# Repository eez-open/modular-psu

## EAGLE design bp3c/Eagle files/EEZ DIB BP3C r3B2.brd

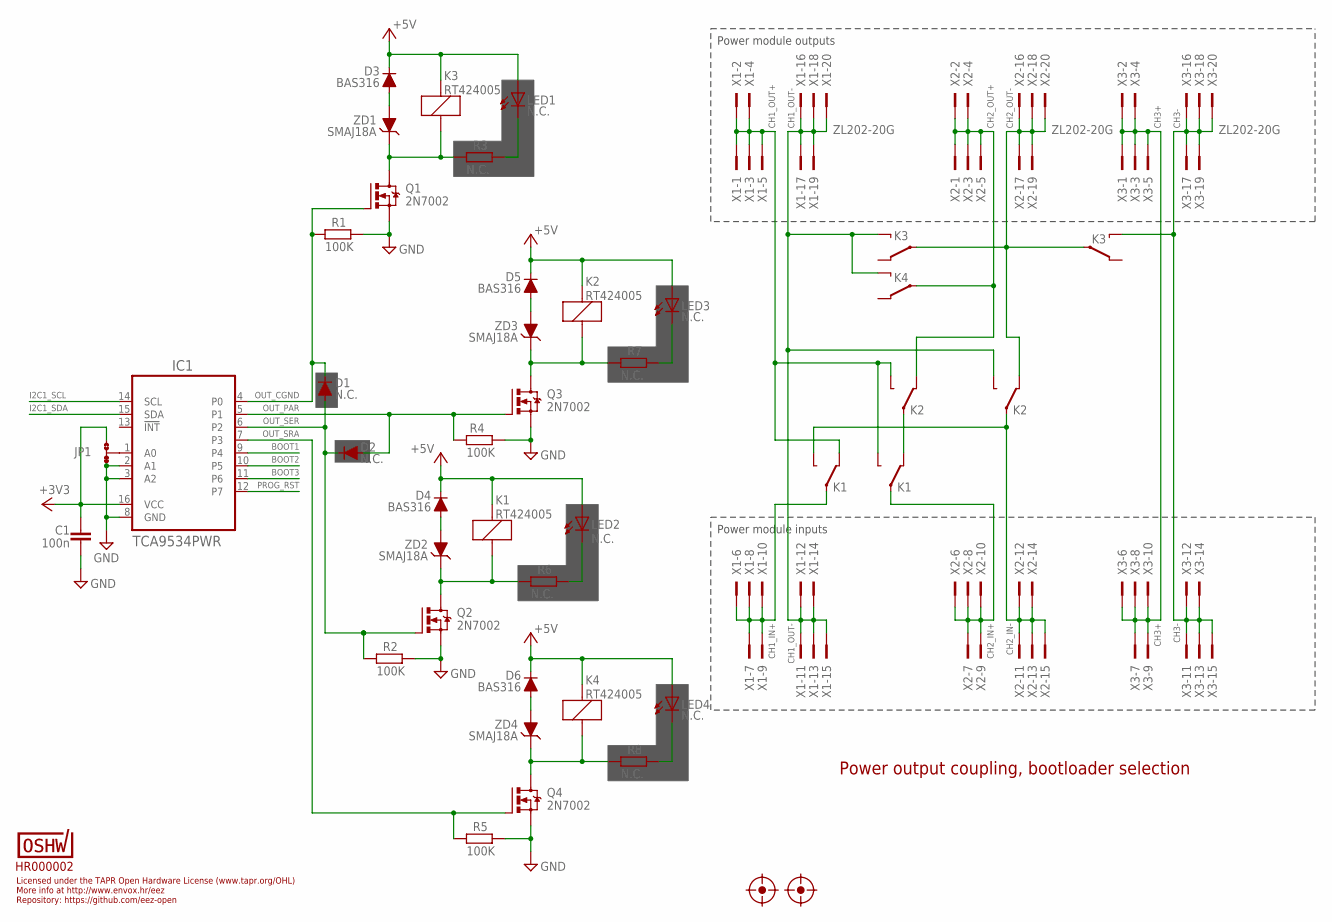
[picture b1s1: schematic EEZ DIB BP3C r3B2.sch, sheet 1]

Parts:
C1: 100n; C0603
D1, D2: N.C.; SOD323-R
D3, D4, D5, D6: BAS316; SOD323-R
FM1, FM2: FIDUCIAL
IC1: TCA9534PWR; PW(R-PDSO-G16)
JP1: JP3-CUT
K1, K2, K3, K4: RT424005; RT-C/016A5_ROUND
LED1, LED2, LED3, LED4: N.C.; LED_0805
OSHWA: HR000002; CERT-SMALL-SILK
Q1, Q2, Q3, Q4: 2N7002; SOT103P240X110-3N; MPN 2N7002-7-F
R1, R2, R4, R5: 100K; R0805
R3, R6, R7, R8: N.C.; R0805
X1, X2, X3: ZL202-20G; DS1021-2*10SF11
ZD1, ZD2, ZD3, ZD4: SMAJ18A; DO214AC

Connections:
+3V3: C1.1, IC1.16 (VCC), JP1.NO; also elsewhere on the board
+5V: D3.C, D4.C, D5.C, D6.C, K1.A2 (C1), K2.A2 (C1), K3.A2 (C1), K4.A2 (C1), LED1.A, LED2.A, LED3.A, LED4.A; also elsewhere on the board
BOOT1: IC1.9 (P4); also elsewhere on the board
BOOT2: IC1.10 (P5); also elsewhere on the board
BOOT3: IC1.11 (P6); also elsewhere on the board
CH1_IN+: K1.11A, X1.6, X1.7, X1.8, X1.9, X1.10
CH1_OUT+: K1.12A (S), K1.14B (O), K2.14A (O), X1.1, X1.2, X1.3, X1.4, X1.5
CH1_OUT-: K2.14B (O), K3.14A (O), K4.14A (O), X1.11, X1.12, X1.13, X1.14, X1.15, X1.16, X1.17, X1.18, X1.19, X1.20
CH2_IN+: K1.11B, X2.6, X2.7, X2.8, X2.9, X2.10
CH2_IN-: K1.14A (O), K2.11B, X2.11, X2.12, X2.13, X2.14, X2.15
CH2_OUT+: K2.12A (S), K4.11A, X2.1, X2.2, X2.3, X2.4, X2.5
CH2_OUT-: K2.12B (S), K3.11A, K3.11B, X2.16, X2.17, X2.18, X2.19, X2.20
CH3+: X3.1, X3.2, X3.3, X3.4, X3.5, X3.6, X3.7, X3.8, X3.9, X3.10
CH3-: K3.14B (O), X3.11, X3.12, X3.13, X3.14, X3.15, X3.16, X3.17, X3.18, X3.19, X3.20
GND: C1.2, IC1.2 (A1), IC1.3 (A2), IC1.8 (GND), JP1.NC, Q1.2 (S), Q2.2 (S), Q3.2 (S), Q4.2 (S), R1.1, R2.1, R4.1, R5.1; also elsewhere on the board
I2C1_SCL: IC1.14 (SCL); also elsewhere on the board
I2C1_SDA: IC1.15 (SDA); also elsewhere on the board
unnamed: LED2.C, R6.1
unnamed: LED3.C, R7.1
unnamed: IC1.1 (A0), JP1.COM
unnamed: K3.A1 (C2), Q1.3 (D), R3.2, ZD1.C
unnamed: D3.A, ZD1.A
unnamed: LED1.C, R3.1
unnamed: K4.A1 (C2), Q4.3 (D), R8.2, ZD4.C
unnamed: D6.A, ZD4.A
unnamed: LED4.C, R8.1
unnamed: K1.A1 (C2), Q2.3 (D), R6.2, ZD2.C
unnamed: K2.A1 (C2), Q3.3 (D), R7.2, ZD3.C
unnamed: D4.A, ZD2.A
unnamed: D5.A, ZD3.A
OUT_CGND: D1.C, IC1.4 (P0), Q1.1 (G), R1.2
OUT_PAR: D2.A, IC1.5 (P1), Q3.1 (G), R4.2
OUT_SER: D1.A, D2.C, IC1.6 (P2), Q2.1 (G), R2.2
OUT_SRA: IC1.7 (P3), Q4.1 (G), R5.2
PROG_RST: IC1.12 (P7); also elsewhere on the board
SER_PAR: K1.12B (S), K2.11A

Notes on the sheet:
Licensed under the TAPR Open Hardware License (www.tapr.org/OHL)
Repository: https://github.com/eez-open
More info at http://www.envox.hr/eez
Power output coupling, bootloader selection
Power module inputs
Power module outputs

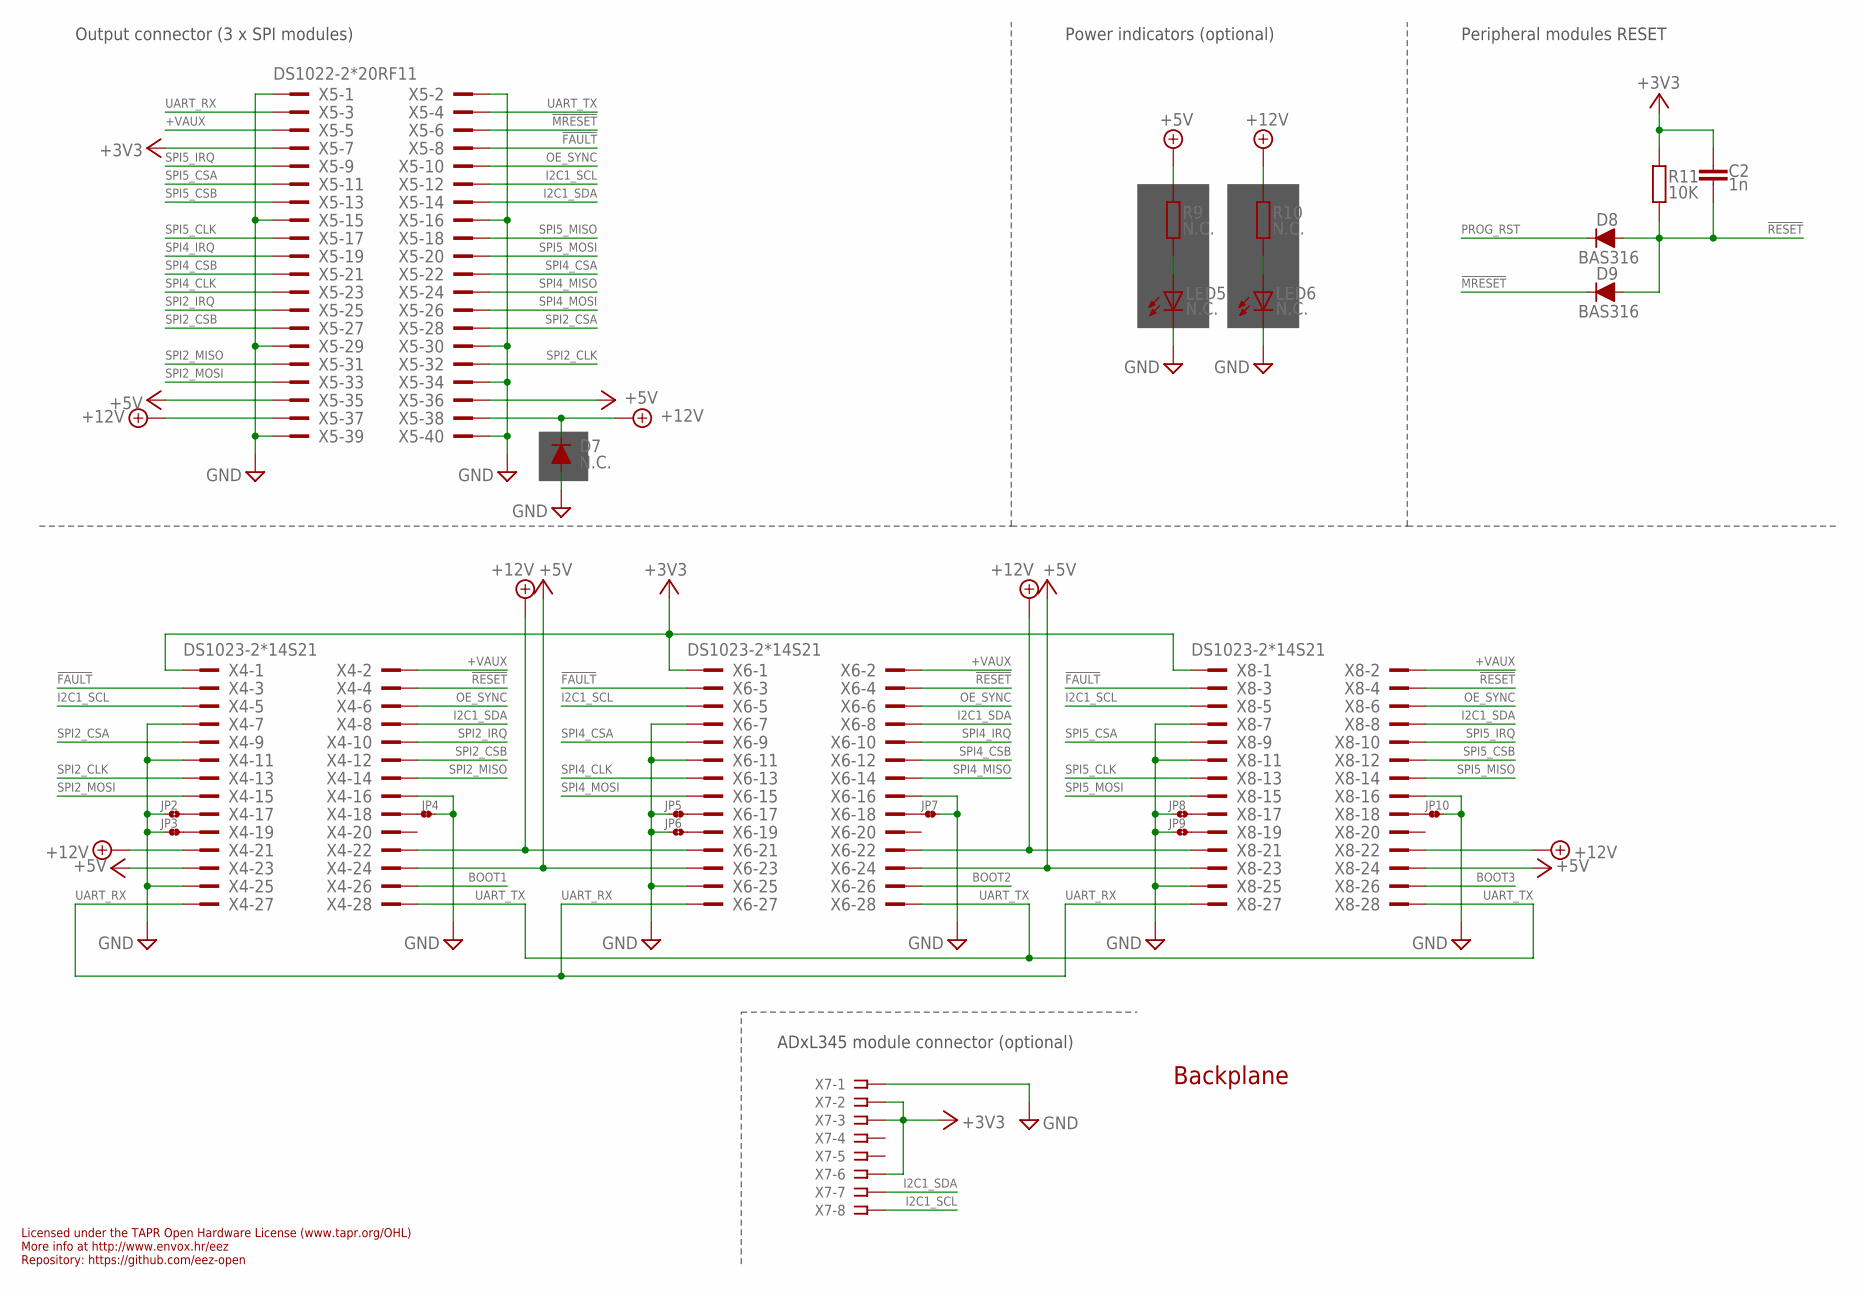
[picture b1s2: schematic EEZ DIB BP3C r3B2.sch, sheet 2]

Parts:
C2: 1n; C0805
D7: N.C.; DO214AA
D8, D9: BAS316; SOD323-R
JP2, JP6, JP8, JP9: JP2-CUT
JP3, JP4, JP5, JP7, JP10: JP2-NOCUT
LED5, LED6: N.C.; LED_0805
R9, R10: N.C.; R0805
R11: 10K; R0805
X4, X6, X8: DS1023-2*14S21; TSW-114-07-F-D
X5: DS1022-2*20RF11; ZL212-40KG
X7: N.C.; SSW-108-02-S-S

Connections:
!FAULT: X4.3, X5.8, X6.3, X8.3
!MRESET: D9.C, X5.6
!RESET: C2.1, D8.A, D9.A, R11.2, X4.4, X6.4, X8.4
+3V3: C2.2, R11.1, X4.1, X5.7, X6.1, X7.2, X7.3, X7.6, X8.1; also elsewhere on the board
+5V: R9.1, X4.23, X4.24, X5.35, X5.36, X6.23, X6.24, X8.23, X8.24; also elsewhere on the board
+12V: D7.C, R10.1, X4.21, X4.22, X5.37, X5.38, X6.21, X6.22, X8.21, X8.22
+VAUX: X4.2, X5.5, X6.2, X8.2
BOOT1: X4.26; also elsewhere on the board
BOOT2: X6.26; also elsewhere on the board
BOOT3: X8.26; also elsewhere on the board
GND: D7.A, JP2.1, JP3.1, JP4.2, JP5.1, JP6.1, JP7.2, JP8.1, JP9.1, JP10.2, LED5.C, LED6.C, X4.7, X4.11, X4.16, X4.25, X5.1, X5.2, X5.15, X5.16, X5.29, X5.30, X5.34, X5.39, X5.40, X6.7, X6.11, X6.16, X6.25, X7.1, X8.7, X8.11, X8.16, X8.25; also elsewhere on the board
I2C1_SCL: X4.5, X5.12, X6.5, X7.8, X8.5; also elsewhere on the board
I2C1_SDA: X4.8, X5.14, X6.8, X7.7, X8.8; also elsewhere on the board
unnamed: JP4.1, X4.18
unnamed: LED5.A, R9.2
unnamed: LED6.A, R10.2
unnamed: JP2.2, X4.17
unnamed: JP3.2, X4.19
unnamed: JP7.1, X6.18
unnamed: JP5.2, X6.17
unnamed: JP6.2, X6.19
unnamed: JP10.1, X8.18
unnamed: JP8.2, X8.17
unnamed: JP9.2, X8.19
OE_SYNC: X4.6, X5.10, X6.6, X8.6
PROG_RST: D8.C; also elsewhere on the board
SPI2_CLK: X4.13, X5.32
SPI2_CSA: X4.9, X5.28
SPI2_CSB: X4.12, X5.27
SPI2_IRQ: X4.10, X5.25
SPI2_MISO: X4.14, X5.31
SPI2_MOSI: X4.15, X5.33
SPI4_CLK: X5.23, X6.13
SPI4_CSA: X5.22, X6.9
SPI4_CSB: X5.21, X6.12
SPI4_IRQ: X5.19, X6.10
SPI4_MISO: X5.24, X6.14
SPI4_MOSI: X5.26, X6.15
SPI5_CLK: X5.17, X8.13
SPI5_CSA: X5.11, X8.9
SPI5_CSB: X5.13, X8.12
SPI5_IRQ: X5.9, X8.10
SPI5_MISO: X5.18, X8.14
SPI5_MOSI: X5.20, X8.15
UART_RX: X4.27, X5.3, X6.27, X8.27
UART_TX: X4.28, X5.4, X6.28, X8.28

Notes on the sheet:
Licensed under the TAPR Open Hardware License (www.tapr.org/OHL)
Repository: https://github.com/eez-open
More info at http://www.envox.hr/eez
Backplane
Output connector (3 x SPI modules)
Power indicators (optional)
Peripheral modules RESET
ADxL345 module connector (optional)

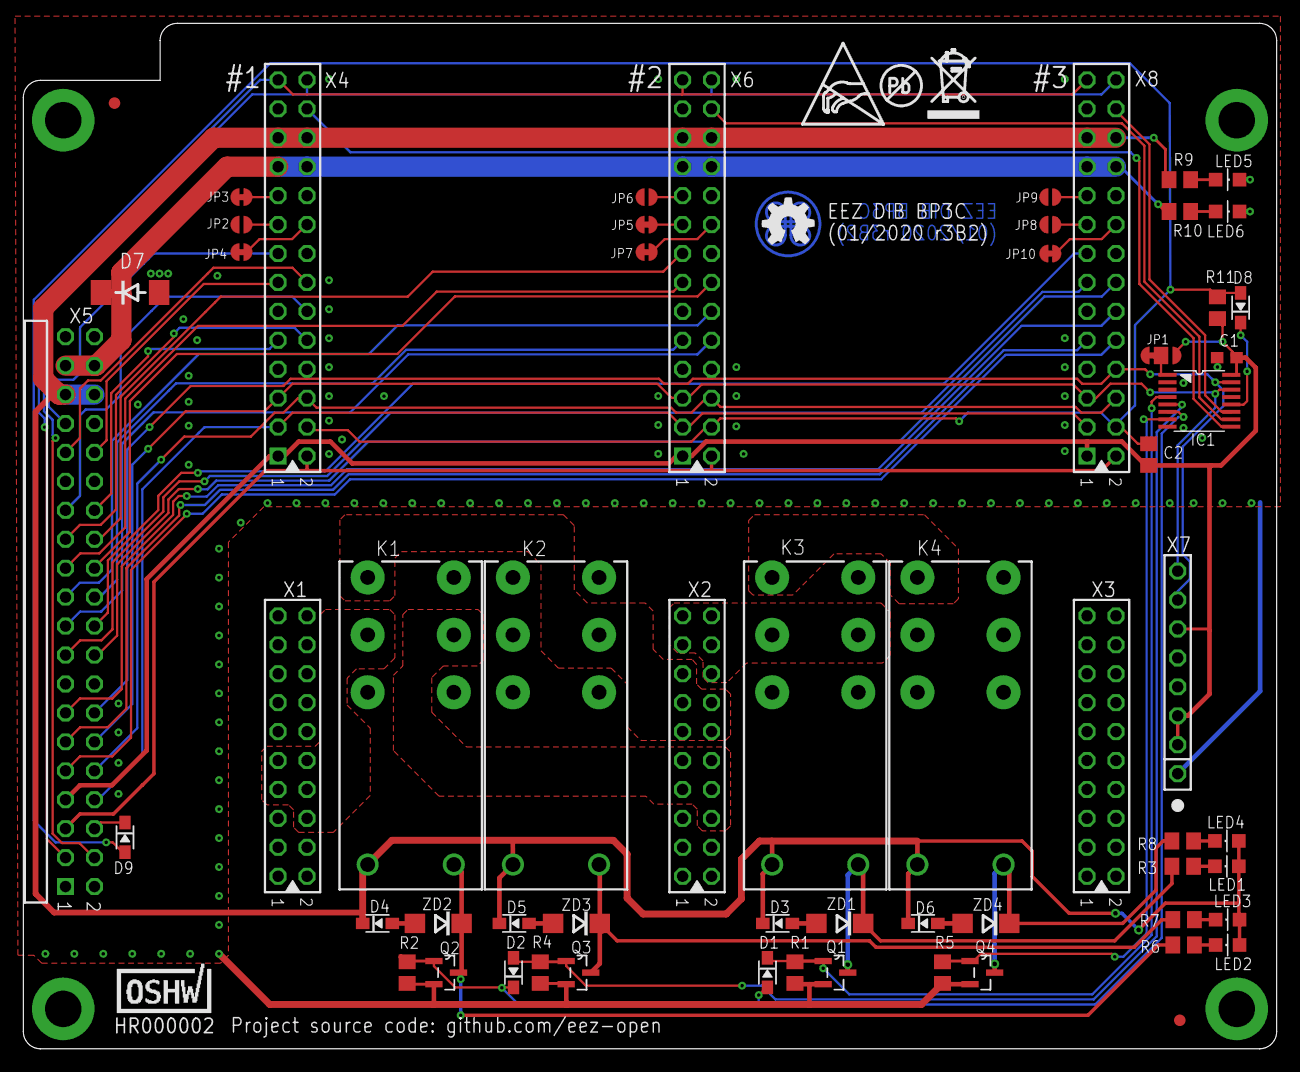
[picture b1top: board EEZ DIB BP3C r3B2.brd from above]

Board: 2 copper layers, 110.0 x 90.0 mm, 66 parts (0 on the bottom side), 73 nets.

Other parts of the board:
EEZ_SIGNATURE: SIGNATURESMALL; SIGNATURE_5MM
U$2: RECYCLE_BIN1/8
U$4: ESD_SYMBOL
U$5: PB_SMALL

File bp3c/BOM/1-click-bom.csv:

References,Qty,Description,Manufacturer,MPN,Manufacturer,MPN,Manufacturer,MPN,Manufacturer,MPN,Manufacturer,MPN,Manufacturer,MPN,Digikey,Mouser,RS,Newark,Farnell
C1,1,100n,,C0603C104K4RAC7081,KEMET,C0603C104K4RAC7081,KEMET,C0603C104K4RACTU,KEMET,C0603C104M4RACTU,Murata,GCM188R71C104KA37D,,,490-4774-6-ND,80C0603C104M4R,2644630,,2522597
C2,1,1n,,VJ0805A102JXACW1BC,Würth Elektronik,885012007040,Würth Elektronik,885012007063,Vishay,VJ0805A102JXACW1BC,,,,,720-1634-6-ND,710885012007063,1927618,,2533866
"D3, D4, D5, D6, D8, D9",6,BAS316,,"BAS316,115",Nexperia,BAS316,Nexperia,"BAS316,115",Nexperia,BAS316Z,,,,,1727-4309-6-ND,771BAS316T/R,3972914,,8734275
IC1,1,TCA9534PWR,Texas Instruments,TCA9534PWR,Texas Instruments,TCA9535PWR,,,,,,,,,296-25129-6-ND,595TCA9535PWR,8143997,,3124760
"K1, K2, K3, K4",4,RT424005,,RT424005,TE Connectivity,5-1393243-9,,,,,,,,,PB1998-ND,655RT424005,,,1629052
"Q1, Q2, Q3, Q4",4,2N7002,,2N7002K-7,ON Semiconductor,2N7002,Diodes Inc.,2N7002K-7,Toshiba,"T2N7002AK,LM",,,,,2N7002K-7DIDKR-ND,5122N7002,6710312,,9845313
"R1, R2, R4, R5",4,100K,,MCWR08X1003FTL,Vishay,CRCW0805100KFKEAC,TE Connectivity,CRG0805F100K,Multicomp,MCWR08X1003FTL,Stackpole Electronics,RMCF0805FT100K,,,RMCF0805FT100KDKR-ND,71CRCW0805100KFKEAC,2230691,,2447551
R11,1,10K,,RC0805FR-0710KL,TE Connectivity,CRG0805F10K,Yageo,RC0805FR-0710KL,,,,,,,311-10.0KCRCT-ND,603RC0805FR0710KL,1251189,,2148862
"X1, X2, X3",3,DS1021-2*10SF11,FCI,77313-802-20LF,,,,,,,,,,,77313-802-20LF-ND,6497731380220LF,,,
X5,1,DS1022-2*20RF11,Amphenol,68020-140HLF,,,,,,,,,,,68020-140HLF-ND,64968020140HLF,,,
"X4, X6, X8",3,DS1023-2*14S21,Sullins,PPTC142LFBN-RC,,,,,,,,,,,S7082-ND,SSQ11401TD,,,
"ZD1, ZD2, ZD3, ZD4",4,SMAJ18A,,SMAJ18A,Bourns,SMAJ18A,Taiwan Semiconductor,SMAJ18A,Diodes Inc.,SMAJ18A-13-F,Vishay,SMAJ18A-E3/61,Bourns,SMAJ18A-Q,SMAJ18A-FDIDKR-ND,621SMAJ18A13F,7103443,,2677644

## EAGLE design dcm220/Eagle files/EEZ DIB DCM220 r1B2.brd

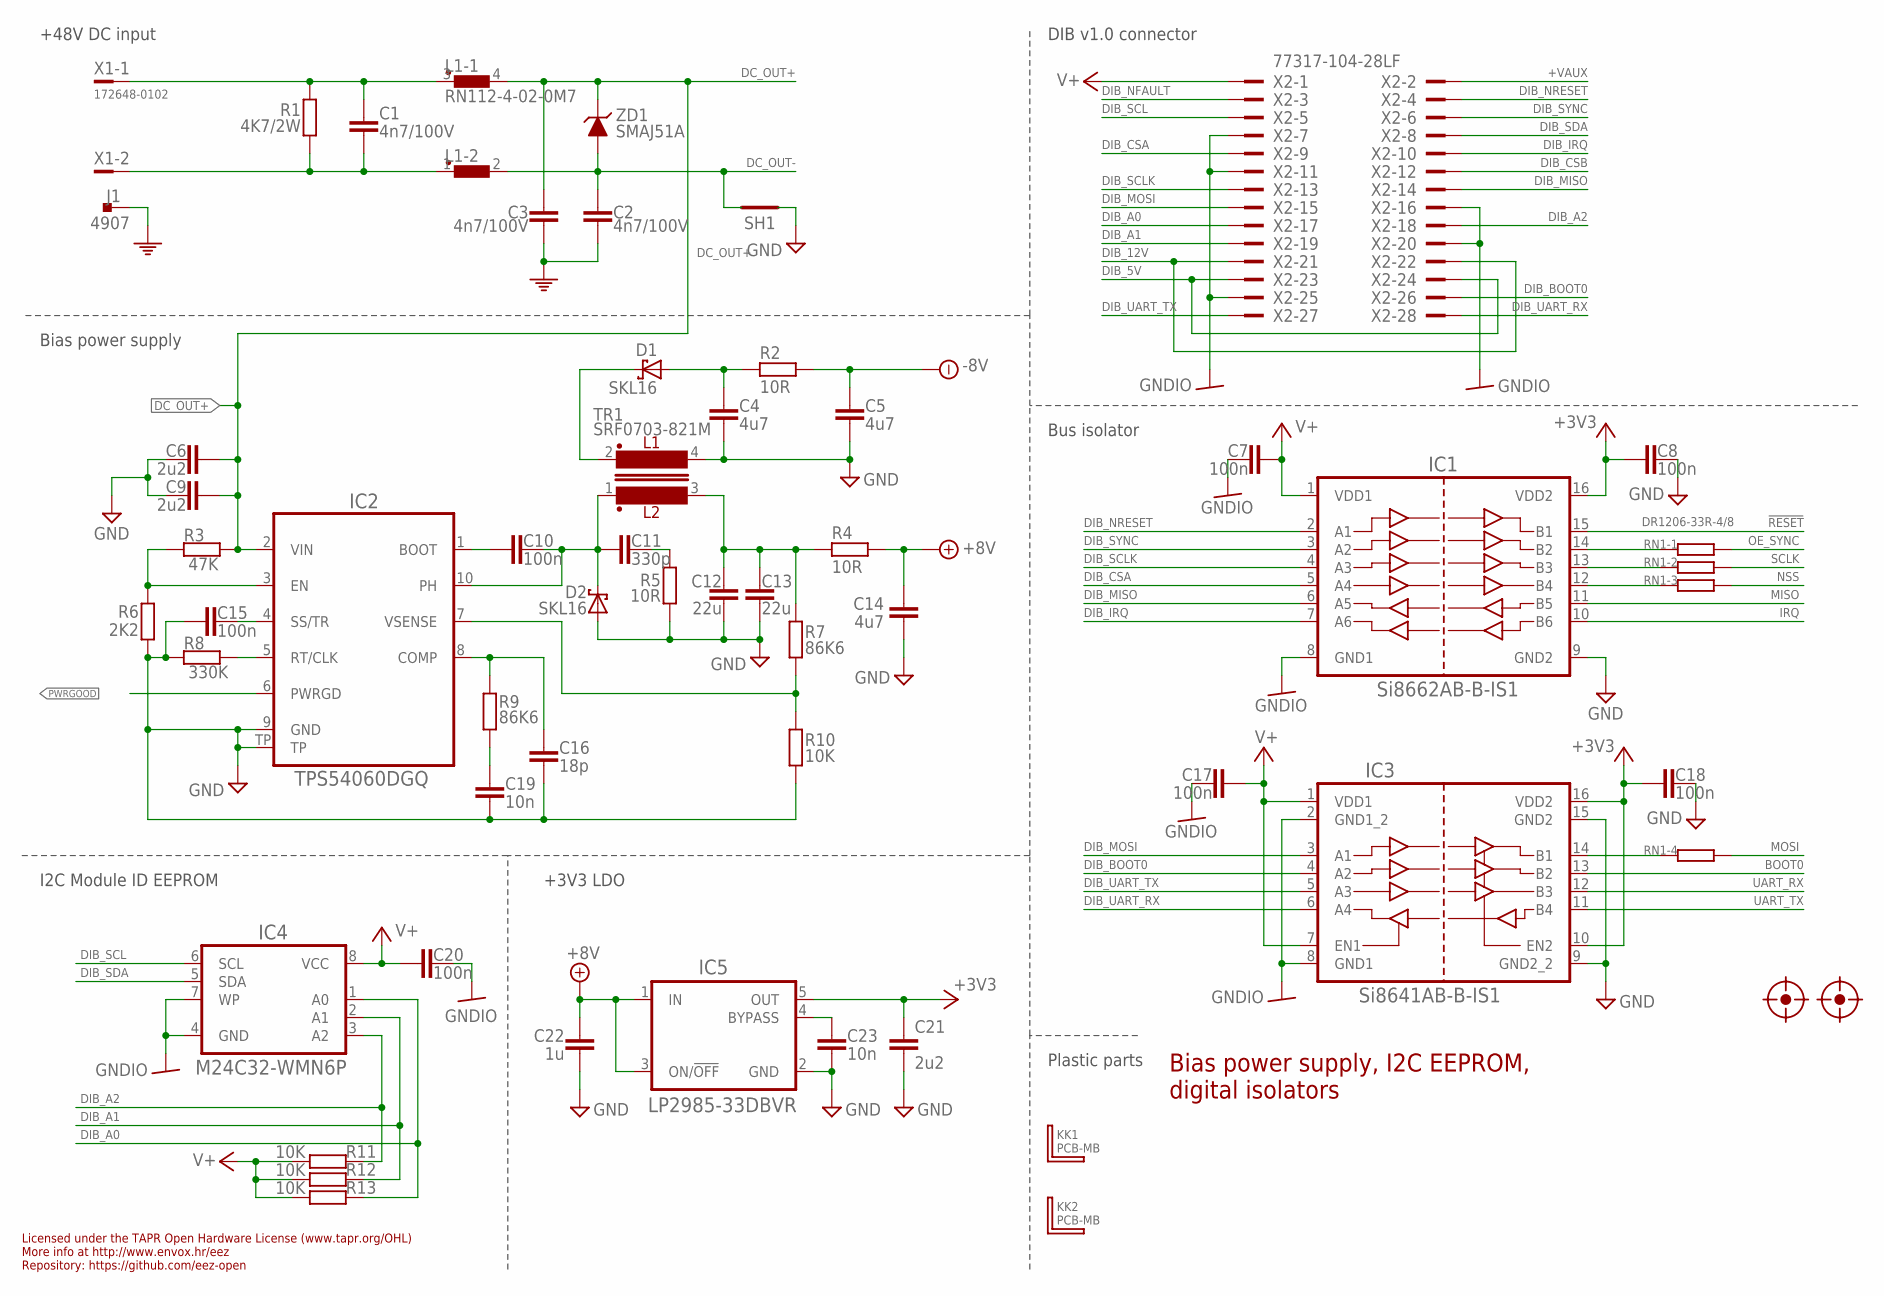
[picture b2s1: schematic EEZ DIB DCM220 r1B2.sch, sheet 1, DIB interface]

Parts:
C1, C2, C3: 4n7/100V; C1206
C4, C5, C14: 4u7; C1206
C6, C9, C21: 2u2; C1206
C7, C8, C10, C15, C17, C18, C20: 100n; C0603
C11: 330p; C0805
C12, C13: 22u; C1206
C16: 18p; C0603
C19, C23: 10n; C0805
C22: 1u; C0805
D1, D2: SKL16; SOD123
FM1, FM2: FIDUCIAL_2; FIDUCIAL_DUAL
IC1: Si8662AB-B-IS1; SOIC-16
IC2: TPS54060DGQ; SOP50P490X110-11N
IC3: Si8641AB-B-IS1; SOIC-16
IC4: M24C32-WMN6P; SOIC127P600X173-8N
IC5: LP2985-33DBVR; SOT95P270X145-5N
J1: 4907; PCB_TAB-4907
KK1, KK2: PCB-MB
L1: RN112-4-02-0M7; RN112
R1: 4K7/2W; R2512
R2, R4, R5: 10R; R0805
R3: 47K; R0805
R6: 2K2; R0805
R7, R9: 86K6; R0805
R8: 330K; R0805
R10, R11, R12, R13: 10K; R0805
RN1: DR1206-33R-4/8; CAY16
SH1: SHORTNOHOLE; SHORT_NOHOLE
TR1: SRF0703-821M; SRF0703
X1: 172648-0102; MINIFIT_39301020
X2: 77317-104-28LF
ZD1: SMAJ51A; DO214AA

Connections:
!RESET: IC1.15 (B1); also elsewhere on the board
+3V3: C8.2, C18.2, C21.1, IC1.16 (VDD2), IC3.10 (EN2), IC3.16 (VDD2), IC5.5 (OUT); also elsewhere on the board
+8V: C14.1, C22.2, IC5.1 (IN), IC5.3 (ON/!OFF), R4.1; also elsewhere on the board
+VAUX: X2.2
-8V: C5.1, R2.1; also elsewhere on the board
BOOT0: IC3.13 (B2); also elsewhere on the board
DC+: C1.2, L1.3 (1), R1.2, X1.1
DC-: C1.1, L1.1, R1.1, X1.2
DC_OUT+: C3.2, C6.1, C9.1, IC2.2 (VIN), L1.4 (2), R3.2, ZD1.C; also elsewhere on the board
DC_OUT-: C2.1, L1.2, SH1.2 (GND_B), ZD1.A; also elsewhere on the board
DIB_5V: X2.23, X2.24
DIB_12V: X2.21, X2.22
DIB_A0: IC4.1 (A0), R13.2, X2.17
DIB_A1: IC4.2 (A1), R12.2, X2.19
DIB_A2: IC4.3 (A2), R11.2, X2.18
DIB_BOOT0: IC3.4 (A2), X2.26
DIB_CSA: IC1.5 (A4), X2.9
DIB_CSB: X2.12
DIB_IRQ: IC1.7 (A6), X2.10
DIB_MISO: IC1.6 (A5), X2.14
DIB_MOSI: IC3.3 (A1), X2.15
DIB_NFAULT: X2.3
DIB_NRESET: IC1.2 (A1), X2.4
DIB_SCL: IC4.6 (SCL), X2.5
DIB_SCLK: IC1.4 (A3), X2.13
DIB_SDA: IC4.5 (SDA), X2.8
DIB_SYNC: IC1.3 (A2), X2.6
DIB_UART_RX: IC3.6 (A4), X2.28
DIB_UART_TX: IC3.5 (A3), X2.27
GND: C4.2, C5.2, C6.2, C8.1, C9.2, C12.2, C13.2, C14.2, C15.2, C16.1, C18.1, C19.1, C21.2, C22.1, C23.1, D2.A, IC1.9 (GND2), IC2.9 (GND), IC2.TP, IC3.9 (GND2_2), IC3.15 (GND2), IC5.2 (GND), R5.1, R6.1, R8.1, R10.1, SH1.1 (GND_A), TR1.4; also elsewhere on the board
GNDIO: C7.2, C17.2, C20.1, IC1.8 (GND1), IC3.2 (GND1_2), IC3.8 (GND1), IC4.4 (GND), IC4.7 (WP), X2.7, X2.11, X2.16, X2.20, X2.25
IRQ: IC1.10 (B6); also elsewhere on the board
MISO: IC1.11 (B5); also elsewhere on the board
MOSI: RN1.5 (2); also elsewhere on the board
unnamed: IC1.14 (B2), RN1.1
unnamed: IC1.13 (B3), RN1.2 (1)
unnamed: IC1.12 (B4), RN1.3 (1)
unnamed: IC3.14 (B1), RN1.4 (1)
unnamed: C23.2, IC5.4 (BYPASS)
unnamed: C4.1, D1.A, R2.2
unnamed: C11.2, R5.2
unnamed: IC2.3 (EN), R3.1, R6.2
unnamed: C15.1, IC2.4 (SS/TR)
unnamed: IC2.5 (RT/CLK), R8.2
unnamed: C16.2, IC2.8 (COMP), R9.2
unnamed: C19.2, R9.1
unnamed: C10.2, IC2.1 (BOOT)
unnamed: IC2.7 (VSENSE), R7.1, R10.2
NSS: RN1.6 (2); also elsewhere on the board
OE_SYNC: RN1.8 (2); also elsewhere on the board
PE: C2.2, C3.1, J1.1, J1.2; also elsewhere on the board
PH1: C10.1, C11.1, D2.C, IC2.10 (PH), TR1.1
PWRGOOD: IC2.6 (PWRGD); also elsewhere on the board
SCLK: RN1.7 (2); also elsewhere on the board
UART_RX: IC3.12 (B3); also elsewhere on the board
UART_TX: IC3.11 (B4); also elsewhere on the board
V+: C7.1, C17.1, C20.2, IC1.1 (VDD1), IC3.1 (VDD1), IC3.7 (EN1), IC4.8 (VCC), R11.1, R12.1, R13.1, X2.1
VOUT+: C12.1, C13.1, R4.2, R7.2, TR1.3
VOUT-: D1.C, TR1.2

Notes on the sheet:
Licensed under the TAPR Open Hardware License (www.tapr.org/OHL)
Repository: https://github.com/eez-open
More info at http://www.envox.hr/eez
I2C Module ID EEPROM
Bias power supply, I2C EEPROM, digital isolators
Plastic parts
Bus isolator
+3V3 LDO
DIB v1.0 connector
Bias power supply
+48V DC input

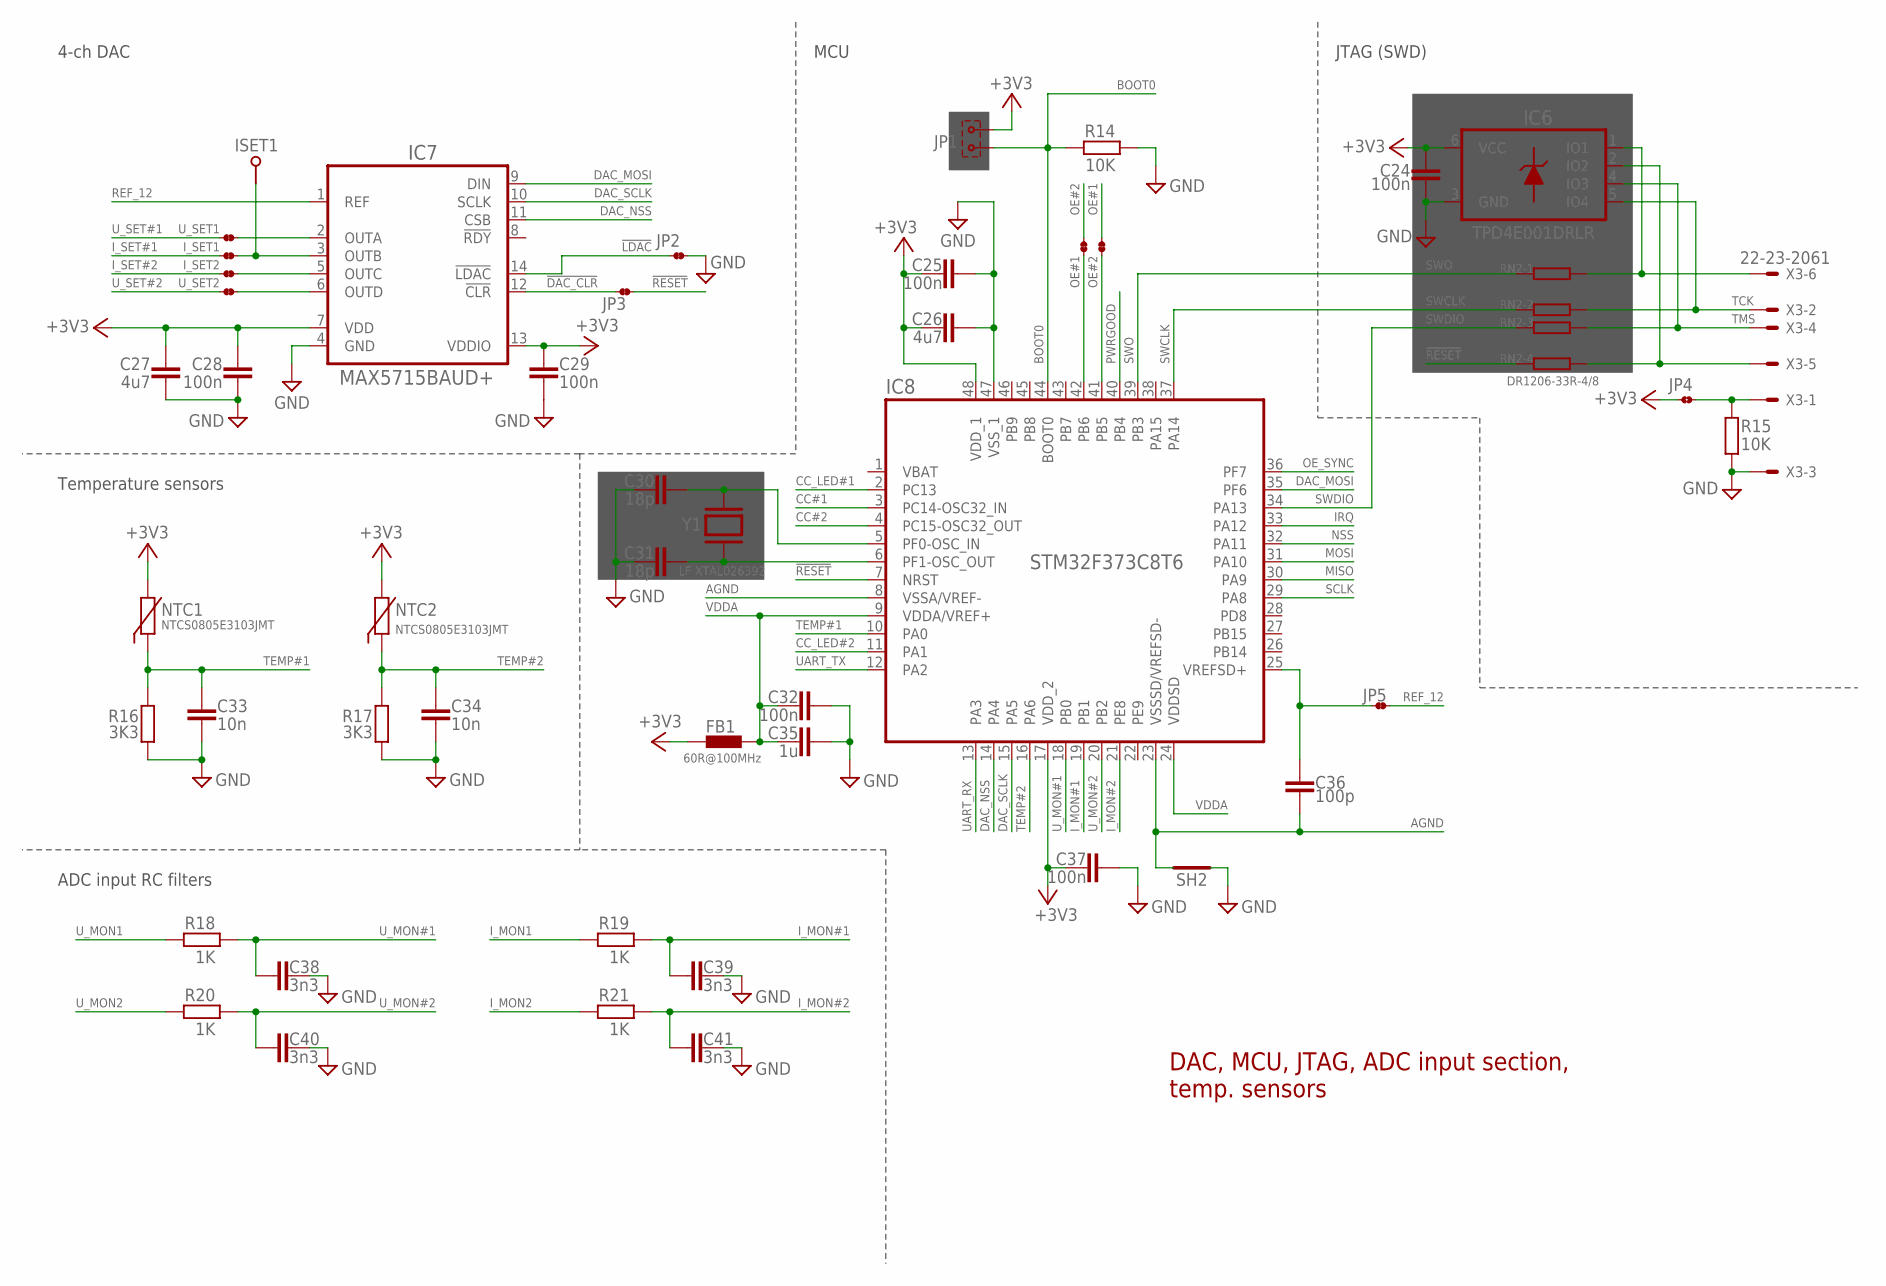
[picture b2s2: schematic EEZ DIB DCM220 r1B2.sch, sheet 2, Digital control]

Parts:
C24, C25, C28, C29, C32, C37: 100n; C0603
C26, C27: 4u7; C1206
C30, C31: 18p; C0603
C33, C34: 10n; C0805
C35: 1u; C0805
C36: 100p; C0805
C38, C39, C40, C41: 3n3; C0805
FB1: 60R@100MHz; BEAD0603
IC6: TPD4E001DRLR; DRL6
IC7: MAX5715BAUD+; 21-0066J_14
IC8: STM32F373C8T6; LQFP-48
ISET1: TEST-PIN_0.9MM
I_SET1, I_SET2: JP2-NOCUT
JP1: JUMPER-2PIN-2MM; 2MM-2
JP2, JP3, JP5: JP2-NOCUT
JP4: JP2-CUT
NTC1, NTC2: NTCS0805E3103JMT; R_0805
OE#1, OE#2: JP2-NOCUT
R14, R15: 10K; R0805
R16, R17: 3K3; R0805
R18, R19, R20, R21: 1K; R0805
RN2: DR1206-33R-4/8; CAY16
SH2: SHORTNOHOLE; SHORT_NOHOLE
U_SET1, U_SET2: JP2-NOCUT
X3: 22-23-2061
Y1: LF XTAL026392; 12SMX(B)

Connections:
!DAC_CLR: IC7.12 (!CLR), JP3.1
!LDAC: IC7.14 (!LDAC), JP2.1
!RESET: IC8.7 (NRST), JP3.2, RN2.4 (1); also elsewhere on the board
+3V3: C24.1, C25.2, C26.1, C27.1, C28.2, C29.2, C37.2, FB1.P$1 (1), IC6.6 (VCC), IC7.7 (VDD), IC7.13 (VDDIO), IC8.17 (VDD_2), IC8.48 (VDD_1), JP1.1, JP4.1, NTC1.1, NTC2.1; also elsewhere on the board
AGND: C36.1, IC8.8 (VSSA/VREF-), IC8.23 (VSSSD/VREFSD-), SH2.1 (GND_A)
BOOT0: IC8.44 (BOOT0), JP1.2, R14.2; also elsewhere on the board
CC#1: IC8.3 (PC14-OSC32_IN); also elsewhere on the board
CC#2: IC8.4 (PC15-OSC32_OUT); also elsewhere on the board
CC_LED#1: IC8.2 (PC13); also elsewhere on the board
CC_LED#2: IC8.11 (PA1); also elsewhere on the board
DAC_MOSI: IC7.9 (DIN), IC8.35 (PF6)
DAC_NSS: IC7.11 (CSB), IC8.14 (PA4)
DAC_SCLK: IC7.10 (SCLK), IC8.15 (PA5)
GND: C24.2, C25.1, C26.2, C27.2, C28.1, C29.1, C30.1, C31.1, C32.1, C33.1, C34.1, C35.1, C37.1, C38.1, C39.1, C40.1, C41.1, IC6.3 (GND), IC7.4 (GND), IC8.47 (VSS_1), JP2.2, R14.1, R15.1, R16.2, R17.2, SH2.2 (GND_B), X3.3; also elsewhere on the board
IRQ: IC8.33 (PA12); also elsewhere on the board
I_MON1: R19.2; also elsewhere on the board
I_MON2: R21.2; also elsewhere on the board
I_MON#1: C39.2, IC8.19 (PB1), R19.1
I_MON#2: C41.2, IC8.21 (PE8), R21.1
I_SET#1: I_SET1.1; also elsewhere on the board
I_SET#2: I_SET2.1; also elsewhere on the board
MISO: IC8.30 (PA9); also elsewhere on the board
MOSI: IC8.31 (PA10); also elsewhere on the board
unnamed: IC7.2 (OUTA), U_SET1.2
unnamed: IC6.1 (IO1), RN2.8 (2), X3.6
unnamed: IC6.2 (IO2), RN2.5 (2), X3.5
unnamed: JP4.2, R15.2, X3.1
unnamed: C36.2, IC8.25 (VREFSD+), JP5.1
unnamed: IC7.3 (OUTB), ISET1.1, I_SET1.2
unnamed: IC7.5 (OUTC), I_SET2.2
unnamed: IC7.6 (OUTD), U_SET2.2
unnamed: IC8.42 (PB6), OE#1.1
unnamed: IC8.41 (PB5), OE#2.1
NSS: IC8.32 (PA11); also elsewhere on the board
OE#1: OE#2.2; also elsewhere on the board
OE#2: OE#1.2; also elsewhere on the board
OE_SYNC: IC8.36 (PF7); also elsewhere on the board
PWRGOOD: IC8.40 (PB4); also elsewhere on the board
RCC_OSC_IN: C30.2, IC8.5 (PF0-OSC_IN), Y1.3 (2)
RCC_OSC_OUT: C31.2, IC8.6 (PF1-OSC_OUT), Y1.1
REF_12: IC7.1 (REF), JP5.2
SCLK: IC8.29 (PA8); also elsewhere on the board
SWCLK: IC8.37 (PA14), RN2.2 (1)
SWDIO: IC8.34 (PA13), RN2.3 (1)
SWO: IC8.39 (PB3), RN2.1
TCK: IC6.5 (IO4), RN2.7 (2), X3.2
TEMP#1: C33.2, IC8.10 (PA0), NTC1.2, R16.1
TEMP#2: C34.2, IC8.16 (PA6), NTC2.2, R17.1
TMS: IC6.4 (IO3), RN2.6 (2), X3.4
UART_RX: IC8.13 (PA3); also elsewhere on the board
UART_TX: IC8.12 (PA2); also elsewhere on the board
U_MON1: R18.2; also elsewhere on the board
U_MON2: R20.2; also elsewhere on the board
U_MON#1: C38.2, IC8.18 (PB0), R18.1
U_MON#2: C40.2, IC8.20 (PB2), R20.1
U_SET#1: U_SET1.1; also elsewhere on the board
U_SET#2: U_SET2.1; also elsewhere on the board
VDDA: C32.2, C35.2, FB1.P$2 (2), IC8.9 (VDDA/VREF+), IC8.24 (VDDSD)

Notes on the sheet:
DAC, MCU, JTAG, ADC input section, temp. sensors
JTAG (SWD)
4-ch DAC
MCU
Temperature sensors
ADC input RC filters

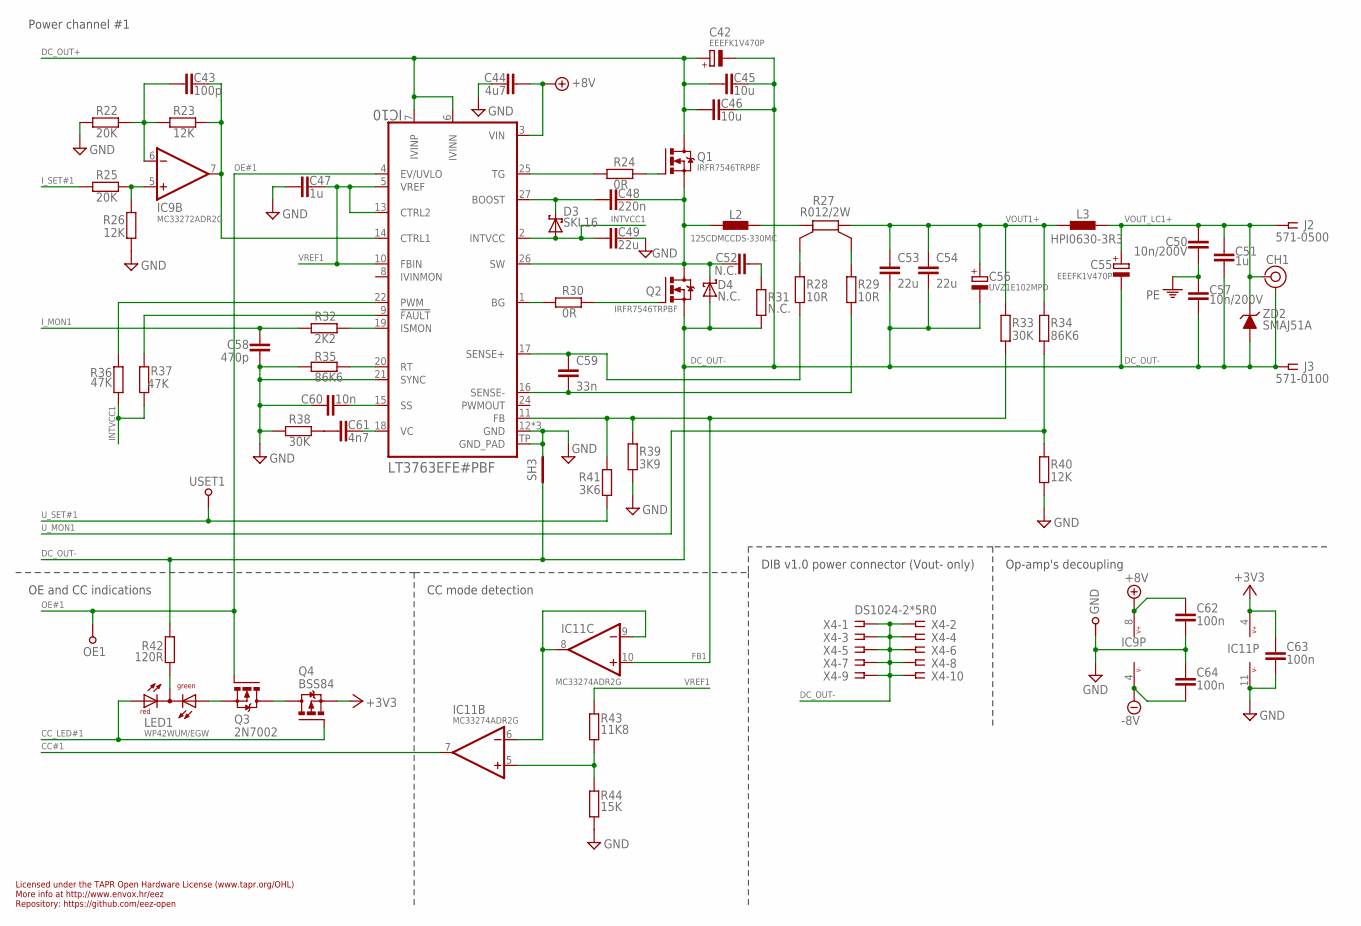
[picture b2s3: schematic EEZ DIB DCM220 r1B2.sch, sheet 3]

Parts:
C42, C55: EEEFK1V470P; CAPAE830X1050N
C43: 100p; C0805
C44: 4u7; C1206
C45, C46: 10u; C1210
C47, C51: 1u; C0805
C48: 220n; C0805
C49, C53, C54: 22u; C1210
C50, C57: 10n/200V; C1206
C52: N.C.; C0805
C56: UVZ1E102MPD; ECAP5/10.5
C58: 470p; C0805
C59: 33n; C0805
C60: 10n; C0805
C61: 4n7; C0805
C62, C63, C64: 100n; C0603
CH1: TEST_POINT-2; TP_1.1MM_2
D3: SKL16; SOD123
D4: N.C.; SMA
GND: TEST-PIN_0.9MM
IC9: MC33272ADR2G; SOIC127P600X173-8N
IC10: LT3763EFE#PBF; LTC_05-08-1663-EB
IC11: MC33274ADR2G; SOIC127P600X175-14N
J2: 571-0500; DELTRON_571
J3: 571-0100; DELTRON_571
L2: 125CDMCCDS-330MC; 125CDMCC/DS
L3: HPI0630-3R3; COILCRAFT_HPI0630
LED1: WP42WUM/EGW; L-42WUM-1EGWT
OE1: TEST-PIN_0.9MM
Q1, Q2: IRFR7546TRPBF; TO229P990X239-3N
Q3: 2N7002; SOT103P240X110-3N
Q4: BSS84; SOT95P237X112-3N
R22, R25: 20K; R0805
R23, R26, R40: 12K; R0805
R24, R30: 0R; R0805
R27: R012/2W; R_2512-4WIRE
R28, R29: 10R; R0805
R31: N.C.; R1206
R32: 2K2; R0805
R33, R38: 30K; R0805
R34, R35: 86K6; R0805
R36, R37: 47K; R0805
R39: 3K9; R0805
R41: 3K6; R0805
R42: 120R; R0805
R43: 11K8; R0805
R44: 15K; R0805
SH3: SHORTNOHOLE; SHORT_NOHOLE
USET1: TEST-PIN_0.9MM
X4: DS1024-2*5R0; SSW-105-02-T-D-RA
ZD2: SMAJ51A; DO214AA

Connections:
+3V3: C63.1, IC11.4 (V+), Q4.2 (S); also elsewhere on the board
+8V: C44.1, C62.1, IC9.8 (V+), IC10.3 (VIN); also elsewhere on the board
-8V: C64.2, IC9.4 (V-); also elsewhere on the board
CC#1: IC11.7 (OUT); also elsewhere on the board
CC_LED#1: LED1.RED (AR), Q4.1 (G); also elsewhere on the board
DC_OUT+: C42.+, C45.1, C46.1, IC10.6 (IVINN), IC10.7 (IVINP), Q1.2 (D); also elsewhere on the board
DC_OUT-: C42.-, C45.2, C46.2, C51.2, C53.2, C54.2, C55.-, C56.-, C57.2, CH1.GND, D4.A, J3.1, J3.1.1, Q2.3 (S), R31.1, R42.2, SH3.1 (GND_A), X4.1, X4.2, X4.3, X4.4, X4.5, X4.6, X4.7, X4.8, X4.9, X4.10, ZD2.A; also elsewhere on the board
FB1: IC10.11 (FB), IC11.10 (+IN), R33.1, R39.2, R41.2
GND: C44.2, C47.2, C49.2, C58.1, C60.1, C62.2, C63.2, C64.1, GND.1, IC10.12 (GND), IC10.21 (SYNC), IC10.23 (GND), IC10.28 (GND), IC10.TP (GND_PAD), IC11.11 (V-), R22.1, R26.1, R35.1, R38.1, R39.1, R40.1, R44.1, SH3.2 (GND_B); also elsewhere on the board
INTVCC1: C49.1, D3.A, IC10.2 (INTVCC), R36.1, R37.2
I_MON1: C58.2, R32.1; also elsewhere on the board
I_SET#1: R25.1; also elsewhere on the board
LOUT1: L2.2, R27.1
unnamed: IC10.1 (BG), R30.1
unnamed: Q2.1 (G), R30.2
unnamed: Q3.3 (D), Q4.3 (D)
unnamed: R27.1S, R28.2
unnamed: IC10.20 (RT), R35.2
unnamed: LED1.CC (C), R42.1
unnamed: C60.2, IC10.15 (SS)
unnamed: C61.1, R38.2
unnamed: C61.2, IC10.18 (VC)
unnamed: IC10.25 (TG), R24.1
unnamed: R27.2S, R29.2
unnamed: C52.2, R31.2
unnamed: IC10.9 (!FAULT), R37.1
unnamed: Q1.1 (G), R24.2
unnamed: C48.1, D3.C, IC10.27 (BOOST)
unnamed: LED1.GREEN (AG), Q3.2 (S)
unnamed: IC10.19 (ISMON), R32.2
unnamed: IC11.5 (+IN), R43.1, R44.2
unnamed: IC11.6 (-IN), IC11.8 (OUT), IC11.9 (-IN)
unnamed: IC9.5 (+IN), R25.2, R26.2
unnamed: C43.2, IC9.6 (-IN), R22.2, R23.1
unnamed: C43.1, IC9.7 (OUT), IC10.14 (CTRL1), R23.2
OE#1: IC10.4 (EV/UVLO), OE1.1, Q3.1 (G); also elsewhere on the board
PE: C50.1, C57.1; also elsewhere on the board
PWM#1: IC10.22 (PWM), R36.2
SENSE1+: C59.1, IC10.17 (SENSE+), R28.1
SENSE1-: C59.2, IC10.16 (SENSE-), R29.1
SW1: C48.2, C52.1, D4.C, IC10.26 (SW), L2.1, Q1.3 (S), Q2.2 (D)
U_MON1: R34.1, R40.2; also elsewhere on the board
U_SET#1: R41.1, USET1.1; also elsewhere on the board
VOUT1+: C53.1, C54.1, C56.+, L3.1, R27.2, R33.2, R34.2
VOUT_LC1+: C50.2, C51.1, C55.+, CH1.TIP, J2.1, J2.1.1, L3.2, ZD2.C
VREF1: C47.1, IC10.5 (VREF), IC10.10 (FBIN), IC10.13 (CTRL2), R43.2

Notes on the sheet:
Licensed under the TAPR Open Hardware License (www.tapr.org/OHL)
Repository: https://github.com/eez-open
More info at http://www.envox.hr/eez
Power channel #1
CC mode detection
DIB v1.0 power connector (Vout- only)
Op-amp's decoupling
OE and CC indications

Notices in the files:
parts and their libraries:
EEZ_DIB: This work is licensed under the TAPR Open Hardware License.
